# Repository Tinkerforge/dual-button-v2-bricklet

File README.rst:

Dual Button Bricklet 2.0
========================

This repository contains the firmware source code and the hardware design
files. The documentation generator configs can be found at
https://github.com/Tinkerforge/generators

Repository Content
------------------

software/:
 * examples/: Examples for all supported languages
 * build/: Compiled files
 * src/: Source code of firmware
 * Makefile: Makefile to build project

hardware/:
 * Contains KiCad project files and additionally schematics as PDF

datasheets/:
 * Contains datasheets for sensors and complex ICs that are used

Hardware
--------

The hardware is designed with the open source EDA Suite KiCad
(http://www.kicad.org). Before you are able to open the files,
you have to install the Tinkerforge kicad-libraries
(https://github.com/Tinkerforge/kicad-libraries). You can either clone
them directly in hardware/ or clone them in a separate folder and
symlink them into hardware/
(ln -s kicad_path/kicad-libraries project_path/hardware). After that you
can open the .pro file in hardware/ with KiCad and from there view and
modify the schematics and the PCB layout.

Software
--------

If you want to do your own Brick/Bricklet firmware development we highly
recommend that you use our build environment setup script and read the
tutorial (https://www.tinkerforge.com/en/doc/Tutorials/Tutorial_Build_Environment/Tutorial.html).

To compile the C code we recommend you to install the newest GNU Arm Embedded
Toolchain (https://launchpad.net/gcc-arm-embedded/+download).
You also need to install bricklib2 (https://github.com/Tinkerforge/bricklib2).

You can either clone it directly in software/src/ or clone it in a
separate folder and symlink it into software/src/
(ln -s bricklib_path/bricklib2 project_path/software/src/). Finally make sure to
have CMake installed (http://www.cmake.org/cmake/resources/software.html).

After that you can build the firmware by invoking make in software/.
The firmware (.zbin) can then be found in software/build/ and uploaded
with brickv (click button "Flashing" on start screen).

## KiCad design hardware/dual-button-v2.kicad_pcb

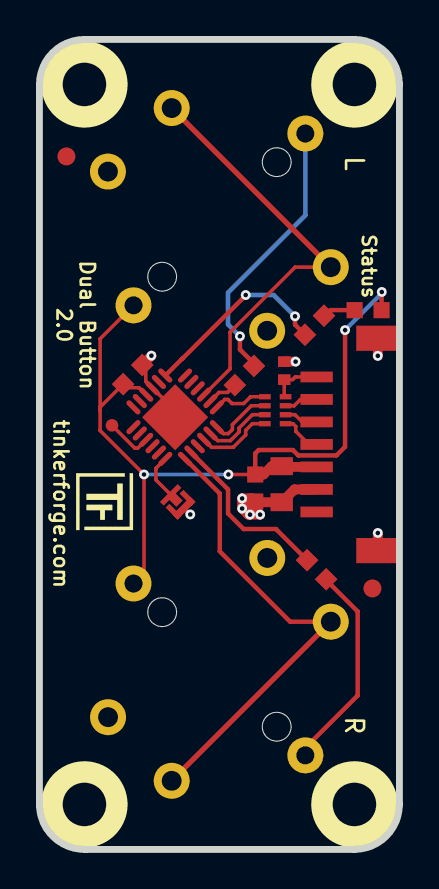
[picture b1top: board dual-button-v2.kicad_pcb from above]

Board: 2 copper layers, 20.0 x 45.0 mm, 24 parts (0 on the bottom side), 20 nets.

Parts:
C1: 10uF; C0805
C2: 220pF; C0402F
C3: 1uF; C0603F
C4: 100nF; C0603F
D1: blue; D0603F
Fiducial_Mark: VAL**; Fiducial_Mark
Fiducial_Mark#2: VAL**; Fiducial_Mark
P1: CON-SENSOR2
P2: DEBUG; DEBUG_PAD
P3: BOOT; SolderJumper
R1, R2, R3: 1k; R0603F
RP2: 82; 4X0402
Ref**: Val**; Logo_31x31
SW1, SW2: TACT_SWITCH_12MM; TACT_SWITCH_12mm
U1: XMC1100; QFN24-4x4mm-0.5mm
U2, U3, U4, U5: DRILL; DRILL_NP
VAL: CE_5mm
VAL#2: WEEE_7mm

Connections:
D1: R2.2, U1.20
D2: R3.2, U1.2
GND: C1.1, C2.1, C3.1, C4.1, P1.2, P1.EP, P3.1, SW1.3, SW2.3, U1.9, U1.EXP
unnamed: C2.2, P1.7, RP2.4
unnamed: D1.2, R1.2
unnamed: P1.4, RP2.1
unnamed: P1.5, RP2.2
unnamed: P1.6, RP2.3
unnamed: P2.1, U1.15
unnamed: P3.2, U1.18
unnamed: R1.1, U1.7
unnamed: R2.1, SW1.2
unnamed: R3.1, SW2.2
S-CLK: RP2.7, U1.23
S-CS: RP2.8, U1.22
S-MISO: RP2.5, U1.1
S-MOSI: RP2.6, U1.24
SW1: SW1.4, U1.19
SW2: SW2.4, U1.3
VCC: C1.2, C3.2, C4.2, D1.1, P1.3, SW1.1, SW2.1, U1.10

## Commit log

2018-02-21 Add schematic
2018-02-21 Add layout
2018-02-23 Add .gitignore
2018-02-23 hardware: Remove special library
2018-03-15 change drilling holes to new standard
2018-04-20 Add auto-generated stub implementation
2018-04-20 Set correct pins for leds/boot pad/debug
2018-04-20 Implement LED/button api and driver
2018-05-11 Rename files
2018-05-25 Add examples
2018-05-28 examples: Unify constant printing style
2018-06-06 fix logo position, fix origin
2018-06-07 fix bottom copper outline
2018-06-18 Change capacitor footprint(s) to C0402F
2018-06-22 Add 3d information (final)
2018-06-22 Add 3d model (*.step & *.FCStd)
2018-06-28 Fix readme
2018-07-11 Add Makefile with docker support
2018-07-11 Remove obsolete generate_makefile scripts
2018-07-11 Update directory structure and build instructions
2018-07-17 specify processor
2018-07-31 Add 3d model (*.FCStd & *.step)
2018-07-31 Add PDF schematic
2018-10-02 Add BOOTLOADER_FIX_POINTER_END define
2018-10-04 Add rev to changelog
2018-10-08 Fix buffer-logic error
2018-10-08 update v2.0.0 rev
2018-10-08 Use correct date
2018-10-16 Remove in-development marker
2018-11-06 Add rust examples
2018-11-07 rust: Accept host names for ip connection, fix naming inconsistencies
2018-11-07 rust: Rename callback receivers.
2018-12-14 Add go examples.
2018-12-18 go: Change import path.
2018-12-18 go: Change import path again.
2018-12-20 rust: Reformat examples.
2019-01-24 mqtt: Add examples.
2019-01-24 mqtt: Fix example header.
2019-01-24 mqtt: Remove executable bit in example permissions.
2019-01-24 go: Minor example fixes.
2019-05-29 Increase version for new release (changes in bricklib2)
2019-08-14 examples: Enable state changed callback.
2019-08-22 c: Adapt to bindings changes
2020-01-13 examples: Use python3 input instead of python2 raw_input.
2020-01-13 examples: mqtt: Remove trailing whitespace.
2020-03-16 Whitespace
2020-04-07 examples: rust: Always block when calling bindings functions.
2020-08-19 Add uc examples.
2020-08-25 uc: Fix whitespace
2020-08-27 uc: Fix warnings.
2020-09-02 uc: Add example driver note.
2021-03-04 increase pad diameter
2021-10-25 Update KiCad link
    https://www.kicad.org/blog/2021/10/Avoid-links-to-former-kicad-domain/
2022-04-19 examples: uc: Rename TF_HalContext to TF_HAL.
2022-04-27 uc: Adapt to bindings changes
2022-07-06 Add license files.
2025-10-04 Fix compatibility with new Docker build image (GCC 14.2.1)

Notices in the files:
hardware/dual-button-v2.kicad_pcb:
Licensed under CERN OHL v.1.1
Copyright (©) 2018, L.Lauer
Copyright Tinkerforge GmbH 2018.
This documentation describes Open Hardware and is licensed under the
CERN OHL v. 1.1.
